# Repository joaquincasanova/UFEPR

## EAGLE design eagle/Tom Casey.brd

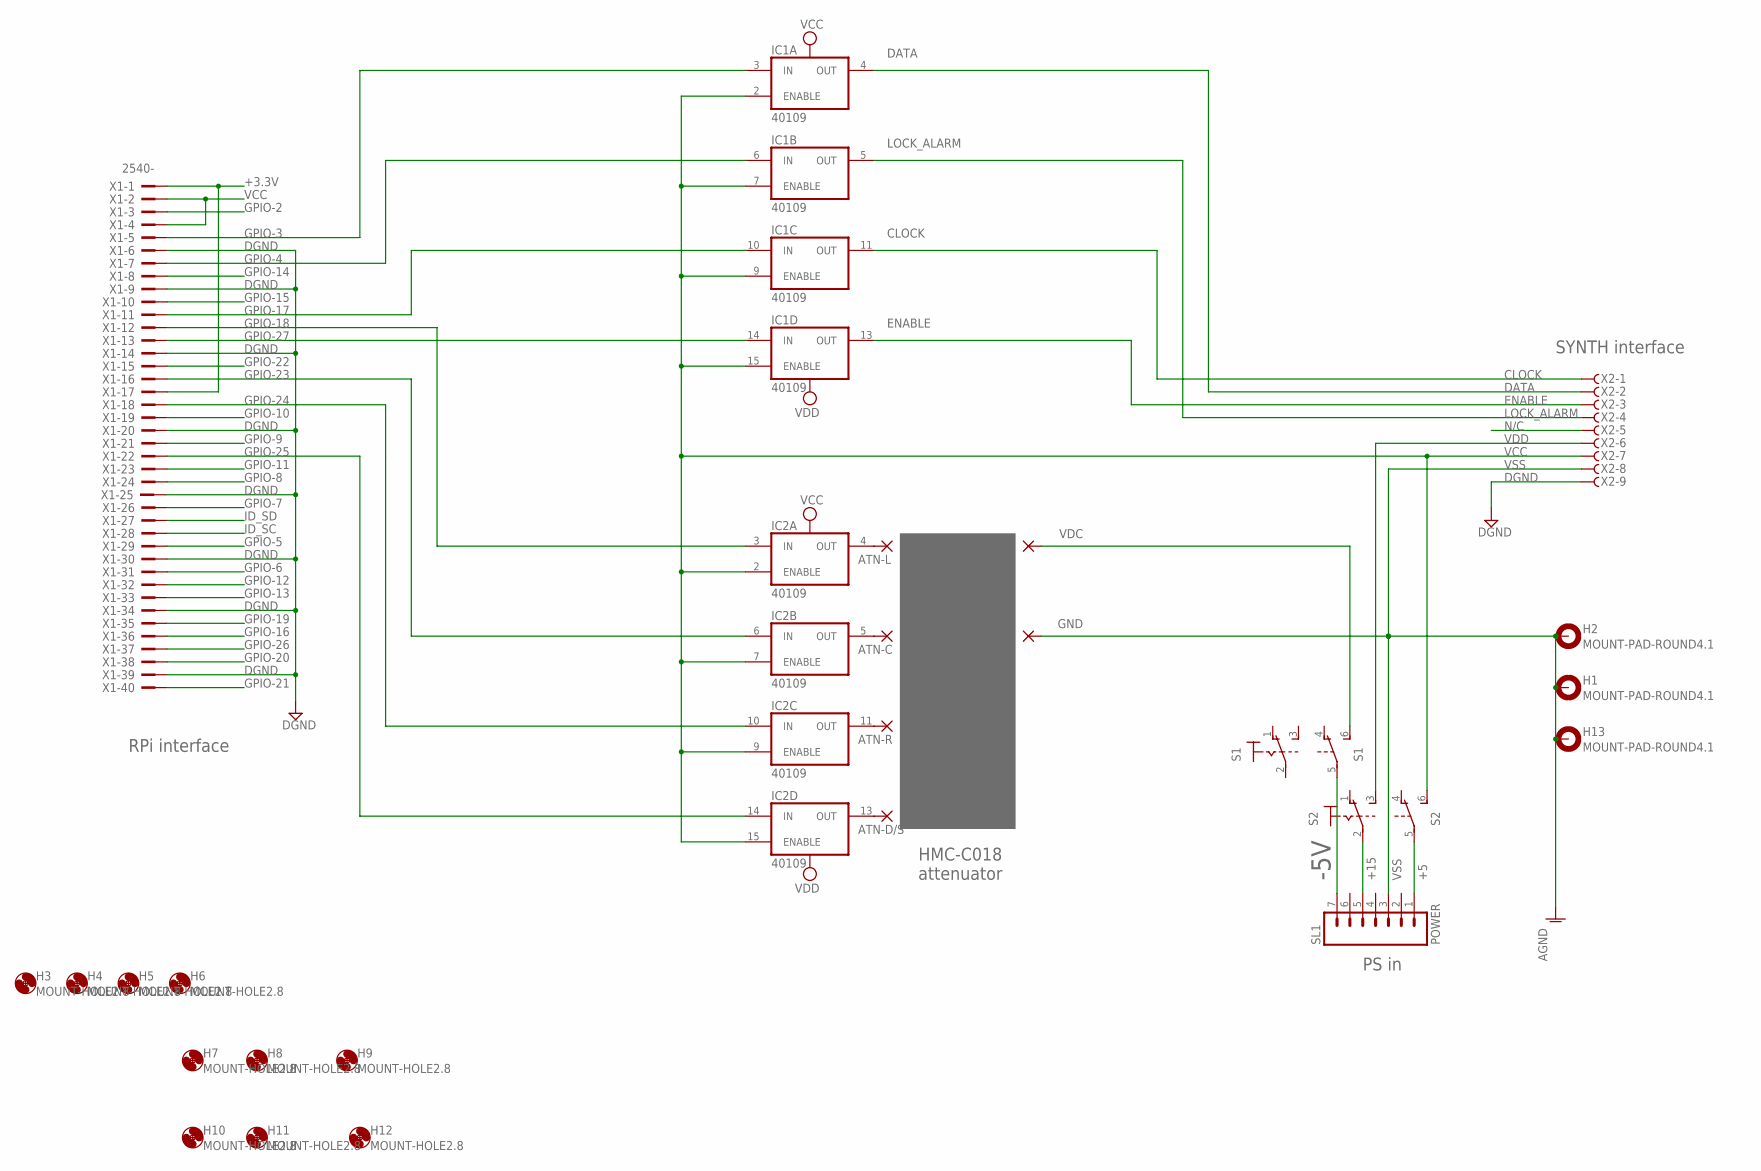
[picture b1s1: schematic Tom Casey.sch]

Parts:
ATN-C: PAD-0400; 0400
ATN-D/S: PAD-0400; 0400
ATN-L: PAD-0400; 0400
ATN-R: PAD-0400; 0400
GND: PAD-0400; 0400
H1, H2, H13: MOUNT-PAD-ROUND4.1; 4,1-PAD
H3, H4, H5, H6, H7, H8, H9, H10, H11, H12: MOUNT-HOLE2.8; 2,8
IC1, IC2: 40109; DIL16
S1, S2: M9040P2
SL1: POWER; 07P
VDC: PAD-0400; 0400
X1: 2540-; PAK100/2500-40
X2: F09HPS; F09HP

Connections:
+3.3V: X1.1, X1.17
+5: S2.5, SL1.1
+15: S2.2, SL1.5
-5V: S1.5, SL1.7
CLOCK: IC1.11 (OUT), X2.1
DATA: IC1.4 (OUT), X2.2
DGND: X1.6, X1.9, X1.14, X1.20, X1.25, X1.30, X1.34, X1.39, X2.9
ENABLE: IC1.13 (OUT), X2.3
GPIO-2: X1.3
GPIO-3: IC1.3 (IN), X1.5
GPIO-4: IC1.6 (IN), X1.7
GPIO-5: X1.29
GPIO-6: X1.31
GPIO-7: X1.26
GPIO-8: X1.24
GPIO-9: X1.21
GPIO-10: X1.19
GPIO-11: X1.23
GPIO-12: X1.32
GPIO-13: X1.33
GPIO-14: X1.8
GPIO-15: X1.10
GPIO-16: X1.36
GPIO-17: IC1.10 (IN), X1.11
GPIO-18: IC2.3 (IN), X1.12
GPIO-19: X1.35
GPIO-20: X1.38
GPIO-21: X1.40
GPIO-22: X1.15
GPIO-23: IC2.6 (IN), X1.16
GPIO-24: IC2.10 (IN), X1.18
GPIO-25: IC2.14 (IN), X1.22
GPIO-26: X1.37
GPIO-27: IC1.14 (IN), X1.13
ID_SC: X1.28
ID_SD: X1.27
LOCK_ALARM: IC1.5 (OUT), X2.4
unnamed: ATN-L.P$1, IC2.4 (OUT)
unnamed: ATN-C.P$1, IC2.5 (OUT)
unnamed: ATN-R.P$1, IC2.11 (OUT)
unnamed: ATN-D/S.P$1, IC2.13 (OUT)
unnamed: S1.6 (S), VDC.P$1
N/C: X2.5
VCC: IC1.1 (VCC), IC1.2 (ENABLE), IC1.7 (ENABLE), IC1.9 (ENABLE), IC1.15 (ENABLE), IC2.1 (VCC), IC2.2 (ENABLE), IC2.7 (ENABLE), IC2.9 (ENABLE), IC2.15 (ENABLE), S2.6 (S), X1.2, X1.4, X2.7
VDD: IC1.16 (VDD), IC2.16 (VDD), S2.3 (S), X2.6
VSS: GND.P$1, H1.B4,1, H2.B4,1, H13.B4,1, IC1.8 (VSS), IC2.8 (VSS), SL1.3, X2.8, X2.G1

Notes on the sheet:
PS in
HMC-C018 attenuator
RPi interface
SYNTH interface

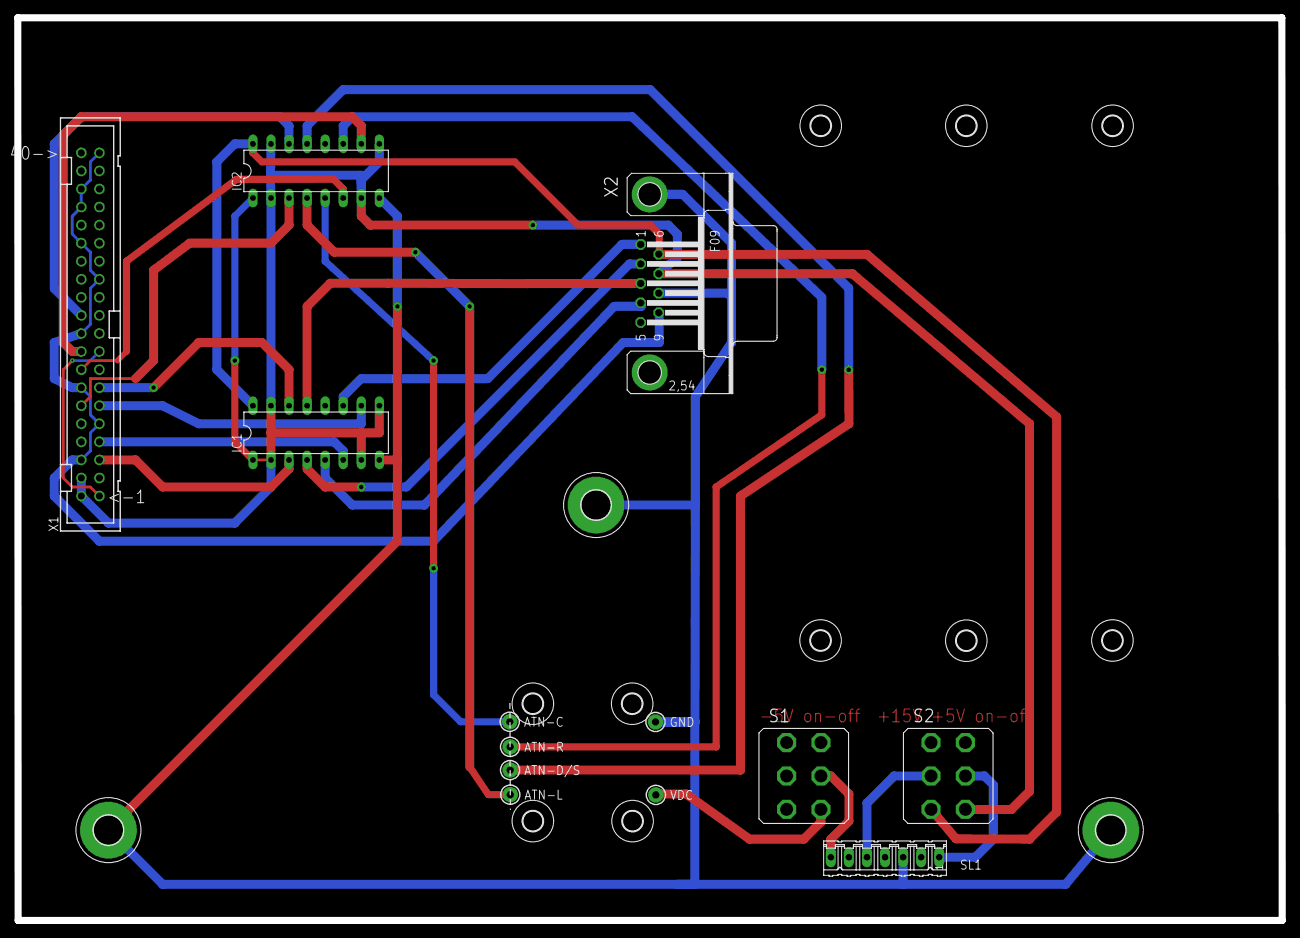
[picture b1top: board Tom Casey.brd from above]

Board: 2 copper layers, 177.8 x 126.9 mm, 26 parts (0 on the bottom side), 25 nets.

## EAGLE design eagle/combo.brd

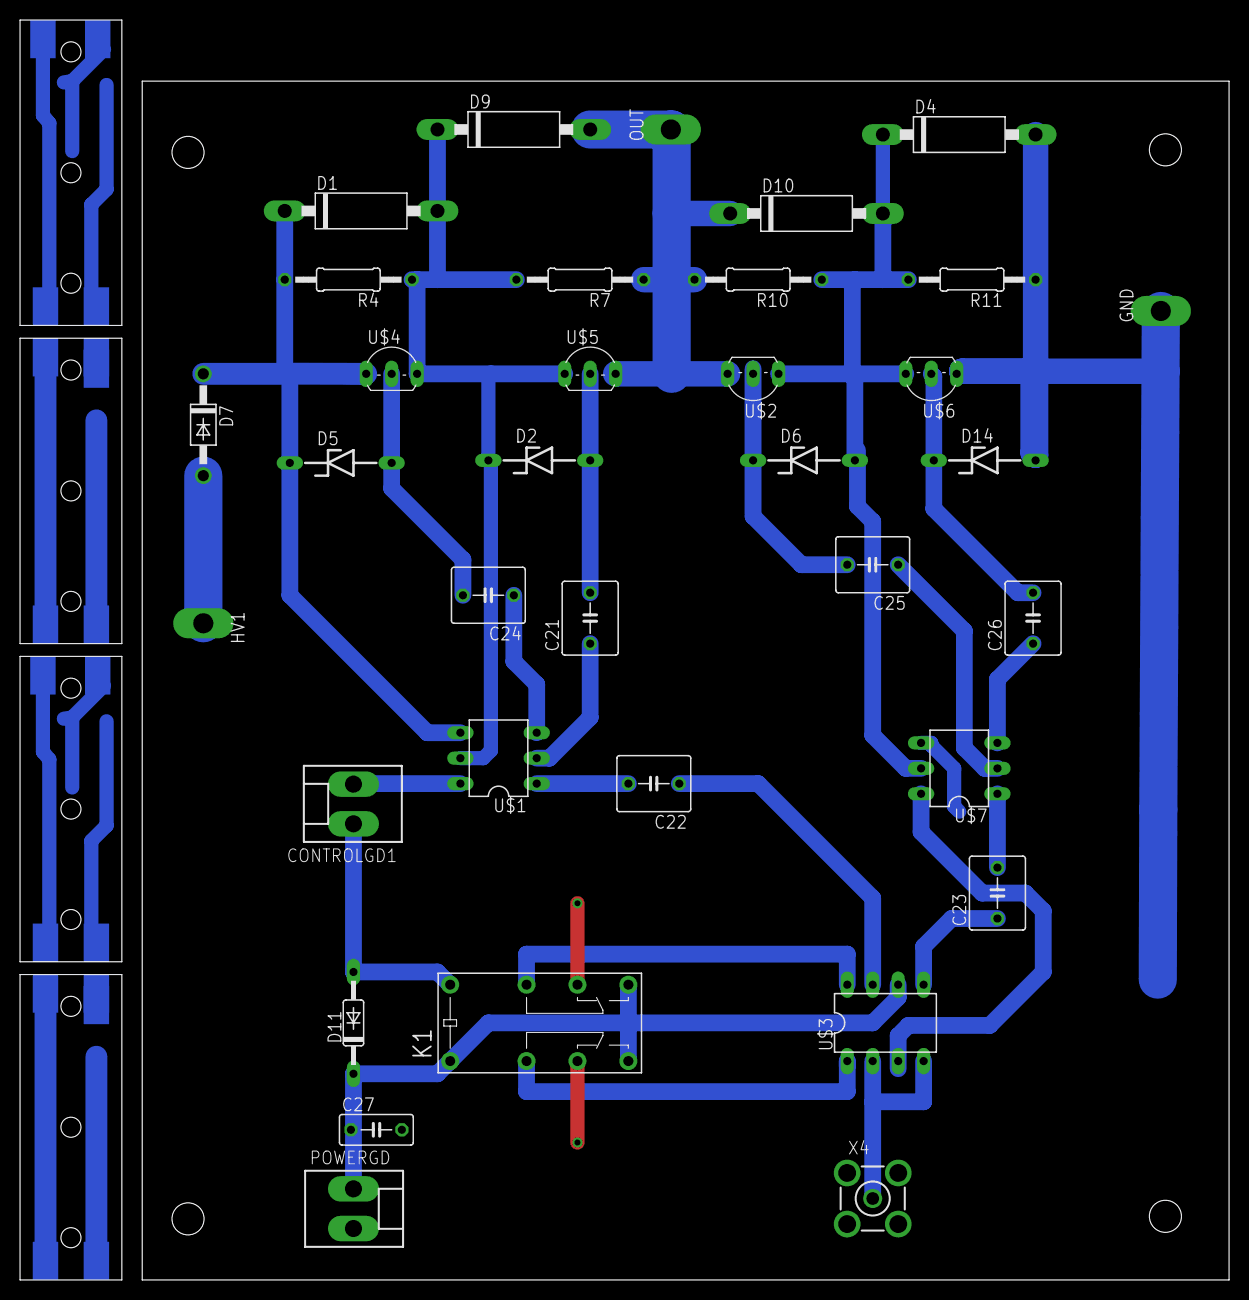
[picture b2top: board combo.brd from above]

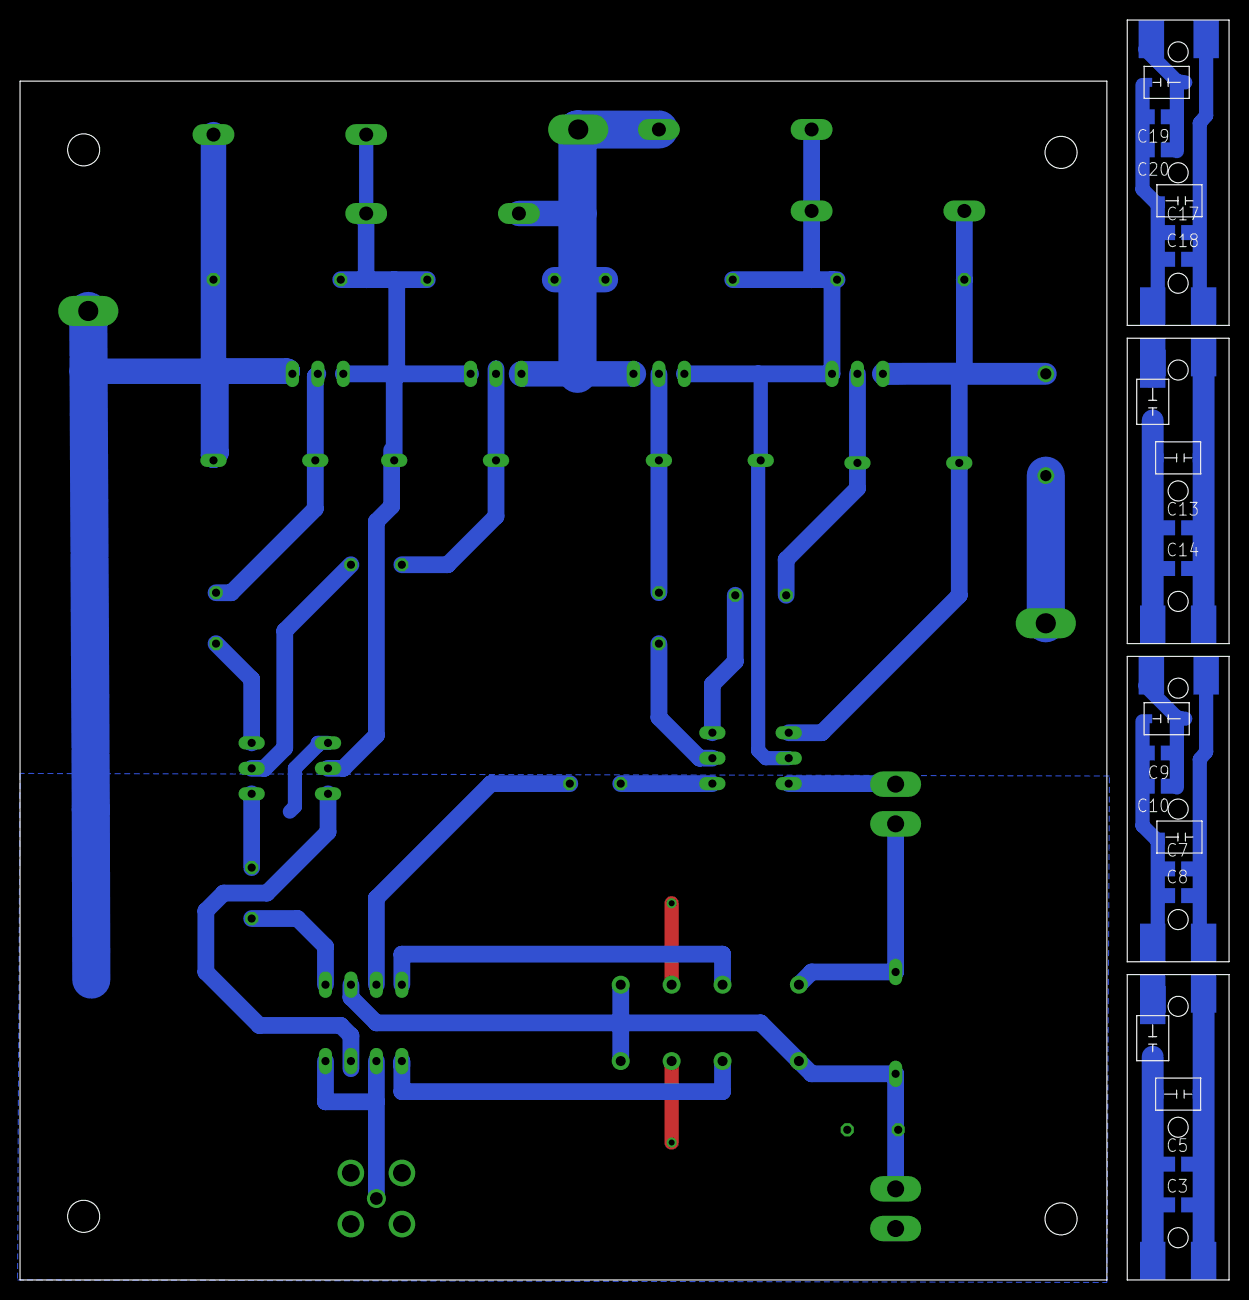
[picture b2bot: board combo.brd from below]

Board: 2 copper layers, 120.7 x 125.7 mm, 55 parts (20 on the bottom side), 33 nets.

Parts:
C1, C4, C6, C11, C15, C16: 5-20; SGC3S
C2, C12: 10-30; SGC3S
C3, C14: 100p; C0805
C5, C13: 50p; C0805
C7, C17: 1000; C0805
C8, C18: 220; C0805
C9, C19: 220p; C0805
C10, C20: 1000p; C0805
C21, C22, C23, C24, C25, C26: C050-055X075
C27: C050-030X075
CONTROLGD1: KK-156-2
D1, D4, D9, D10: P6KEXXA; C1702-15
D2, D5, D6, D14: 4742; ZDIO-10
D7: 1N4004; DO41-10
D11: 1N4148DO35-10; DO35-10
GND: TPPAD1-20Y; P1-20Y
HV1: TPPAD1-20Y; P1-20Y
K1: G5V-2
OUT: TPPAD1-20Y; P1-20Y
POWERGD: KK-156-2
R4, R7, R10, R11: 10M; 0207/12
U$1, U$7: DA-2320; DIL06
U$2, U$6: VN0550; TO92-
U$3: UCC27425; DIL08
U$4, U$5: VP0550; TO92-
X4: BU-SMA-V

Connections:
+15V: C27.1, D11.C, K1.1, K1.8, K1.9, POWERGD.1, U$3.6
ENSW: CONTROLGD1.1, D11.A, K1.16
GND: C27.2, CONTROLGD1.2, D4.A, D14.A, GND.TP, K1.6, K1.11, POWERGD.2, R11.1, U$1.6, U$3.3, U$6.3, U$7.4, U$7.6, X4.2, X4.3, X4.4, X4.5
unnamed: C1.P$1, C2.P$2, C3.1, C5.1
unnamed: C4.P$1, C6.P$2, C7.1, C8.1, C9.2, C10.2
unnamed: C4.P$2, C9.1, C10.1
unnamed: C7.2, C8.2
unnamed: C11.P$1, C12.P$2, C13.1, C14.1
unnamed: C3.2, C5.2
unnamed: C13.2, C14.2
unnamed: C15.P$1, C16.P$2, C17.1, C18.1, C19.2, C20.2
unnamed: C15.P$2, C19.1, C20.1
unnamed: C17.2, C18.2
unnamed: U$3.2, U$3.4, X4.1
unnamed: C22.2, U$1.1
unnamed: C22.1, U$3.7
unnamed: C23.1, U$3.5
unnamed: K1.4, U$3.1
unnamed: K1.13, U$3.8
unnamed: C21.1, U$1.2
unnamed: C24.1, U$1.3
unnamed: C21.2, D2.A, U$5.2
unnamed: C25.1, U$7.2
unnamed: C26.1, U$7.3
unnamed: C24.2, D5.A, U$4.2
unnamed: C25.2, D6.C, U$2.2
unnamed: D1.C, D5.C, D7.C, R4.2, U$1.4, U$4.3
unnamed: C26.2, D14.C, U$6.2
unnamed: D9.A, D10.C, OUT.TP, R7.1, R10.2, U$2.1, U$5.1
unnamed: D7.A, HV1.TP
unnamed: C23.2, U$7.1
unnamed: D4.C, D6.A, D10.A, R10.1, R11.2, U$2.3, U$6.1
unnamed: D1.A, D2.C, D9.C, R4.1, R7.2, U$1.5, U$4.1, U$5.3

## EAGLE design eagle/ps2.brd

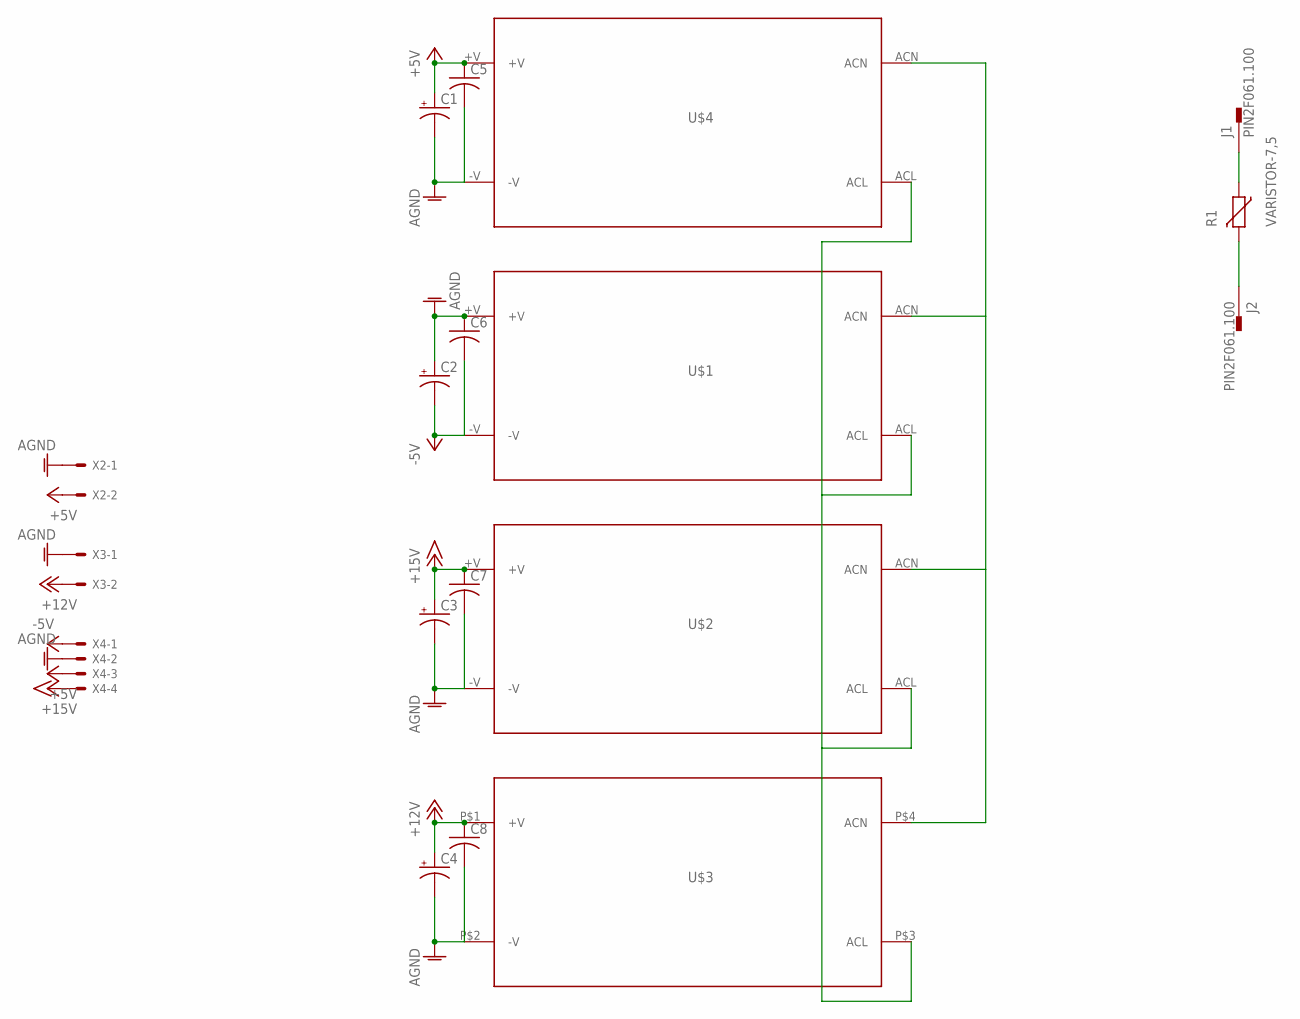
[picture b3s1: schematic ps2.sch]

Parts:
C1, C2, C3, C4: CPOL-USE10-22.5; EB22,5D
C5, C6, C7, C8: C-US075-052X106; C075-052X106
J1, J2: PIN2F061.100; F061.100
R1: VARISTOR-7,5; R-7,5
U$1, U$4: IRM-30-5; IRM-30-15
U$2: IRM-30-15
U$3: IRM-60-12
X2, X3: KK-156-2
X4: KK-156-4

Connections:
+5V: C1.+, C5.1, U$4.+V, X2.2, X4.3
+12V: C4.+, C8.1, U$3.P$1 (+V), X3.2
+15V: C3.+, C7.1, U$2.+V, X4.4
-5V: C2.-, C6.2, U$1.-V, X4.1
ACL: J1.A1, J1.A2, R1.1, U$1.ACL, U$2.ACL, U$3.P$3 (ACL), U$4.ACL
ACN: J2.A1, J2.A2, R1.2, U$1.ACN, U$2.ACN, U$3.P$4 (ACN), U$4.ACN
AGND: C1.-, C2.+, C3.-, C4.-, C5.2, C6.1, C7.2, C8.2, U$1.+V, U$2.-V, U$3.P$2 (-V), U$4.-V, X2.1, X3.1, X4.2

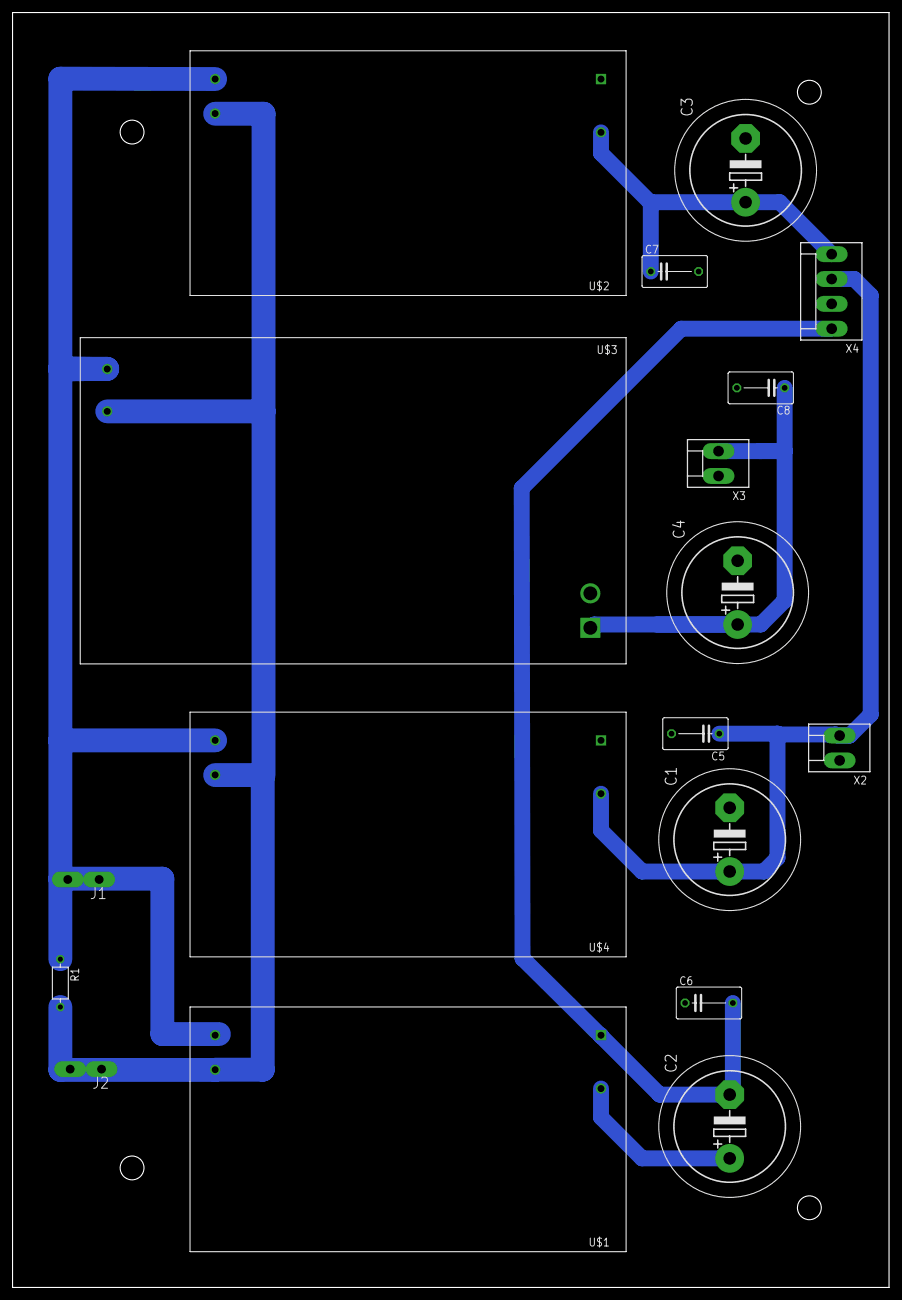
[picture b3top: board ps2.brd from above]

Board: 2 copper layers, 139.7 x 203.2 mm, 18 parts (0 on the bottom side), 7 nets.

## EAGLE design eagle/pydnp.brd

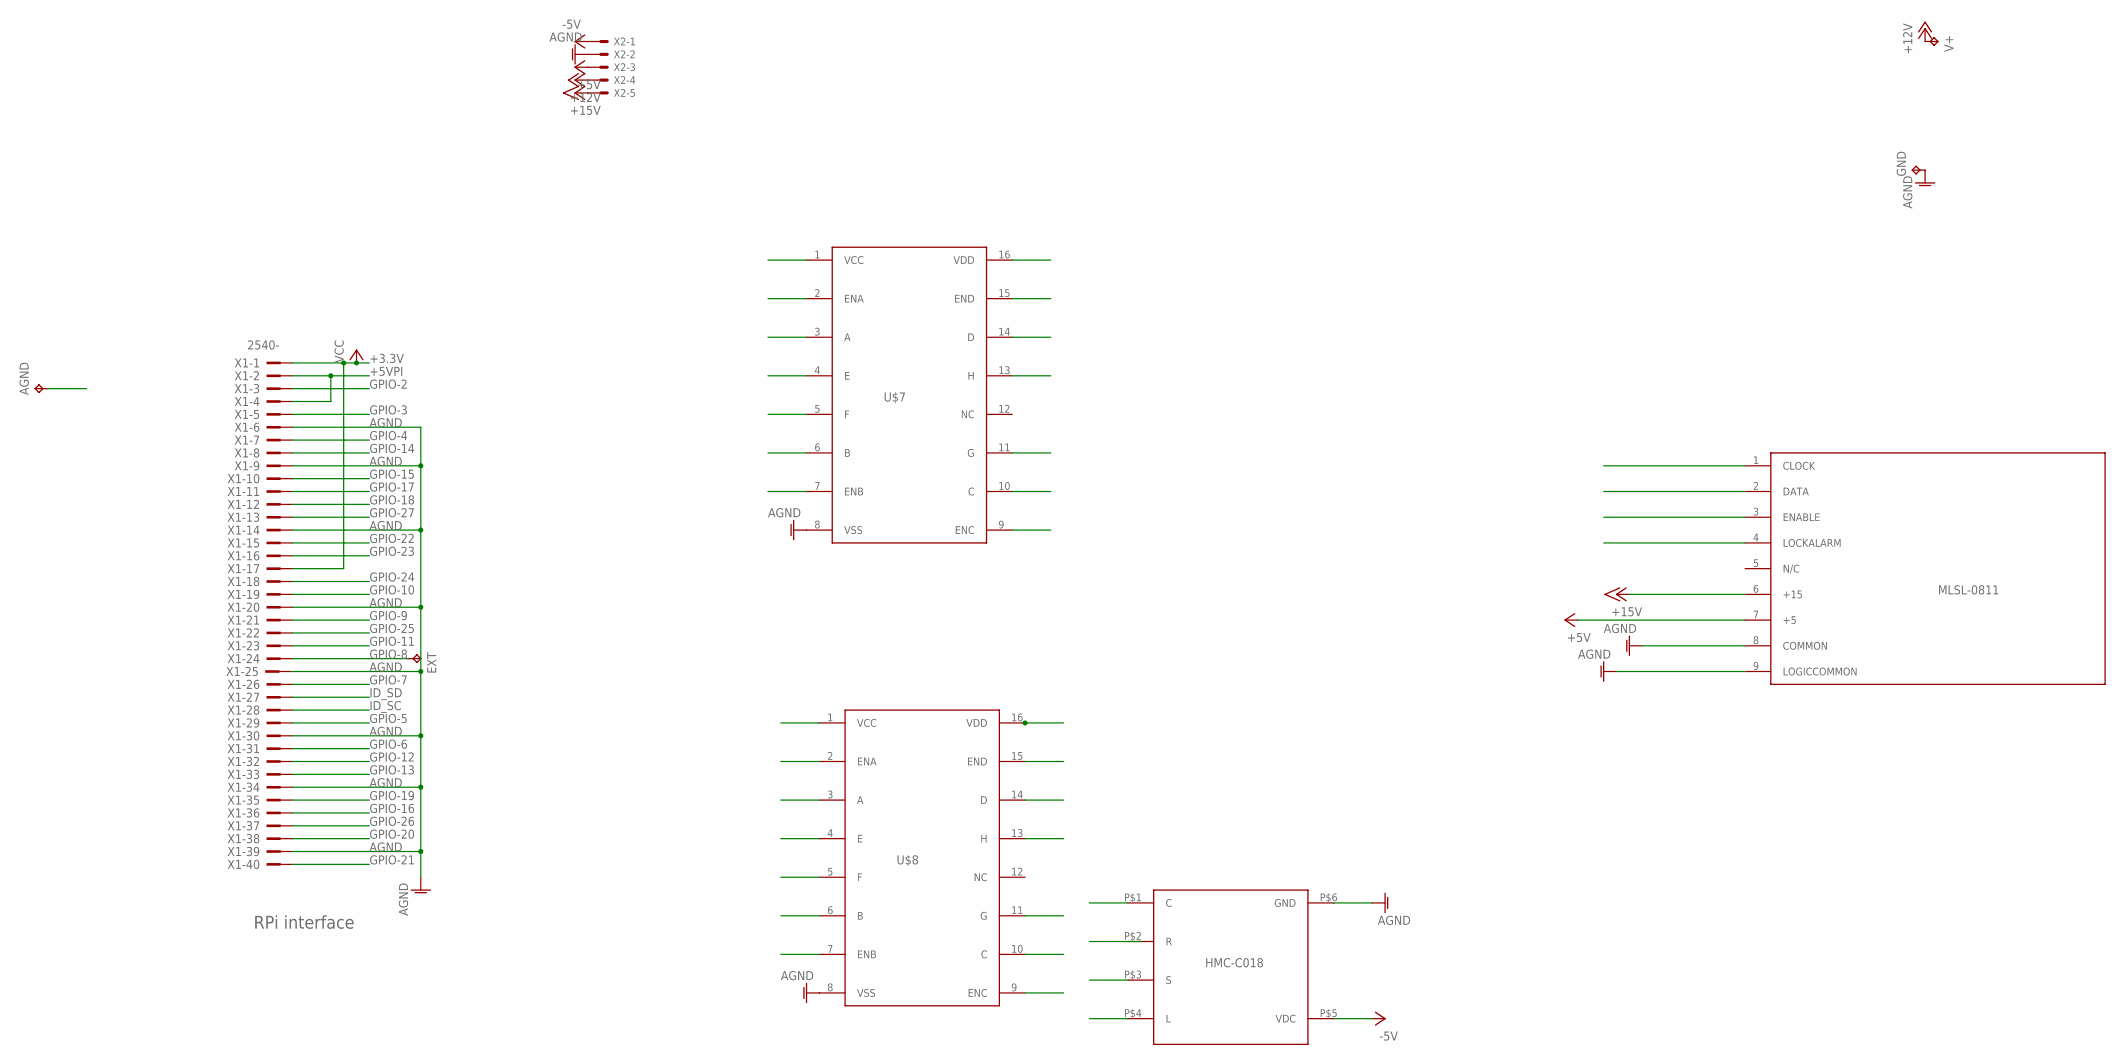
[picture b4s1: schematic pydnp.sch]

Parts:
AGND: TPPAD1-20Y; P1-20Y
EXT: TPPAD1-20Y; P1-20Y
GND: TPPAD1-20Y; P1-20Y
U$1: MLSLCORRECT; 177-009-FEMALE
U$2: HMC-C018
U$7, U$8: 40109; DIL16
V+: TPPAD1-20Y; P1-20Y
X1: 2540-; PAK100/2500-40
X2: KK-156-5

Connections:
+3.3V: U$7.1 (VCC), U$7.2 (ENA), U$7.7 (ENB), U$7.9 (ENC), U$7.15 (END), U$8.1 (VCC), U$8.2 (ENA), U$8.7 (ENB), U$8.9 (ENC), U$8.15 (END), X1.1, X1.17
+5V: U$1.7 (+5), X2.3
+5VPI: U$7.16 (VDD), U$8.16 (VDD), X1.2, X1.4
+12V: V+.TP, X2.4
+15V: U$1.6 (+15), X2.5
-5V: U$2.P$5 (VDC), X2.1
AGND: AGND.TP, GND.TP, U$1.8 (COMMON), U$1.9 (LOGICCOMMON), U$2.P$6 (GND), U$7.8 (VSS), U$8.8 (VSS), X1.6, X1.9, X1.14, X1.20, X1.25, X1.30, X1.34, X1.39, X2.2
C: U$2.P$1 (C), U$8.4 (E)
CLOCK: U$1.1 (CLOCK), U$7.4 (E)
DATA: U$1.2 (DATA), U$7.13 (H)
ENABLE: U$1.3 (ENABLE), U$7.11 (G)
GPIO-2: X1.3
GPIO-3: X1.5
GPIO-4: U$7.10 (C), X1.7
GPIO-5: X1.29
GPIO-6: X1.31
GPIO-7: X1.26
GPIO-8: EXT.TP, X1.24
GPIO-9: X1.21
GPIO-10: X1.19
GPIO-11: X1.23
GPIO-12: X1.32
GPIO-13: X1.33
GPIO-14: X1.8
GPIO-15: X1.10
GPIO-16: X1.36
GPIO-17: U$7.6 (B), X1.11
GPIO-18: U$8.14 (D), X1.12
GPIO-19: X1.35
GPIO-20: X1.38
GPIO-21: X1.40
GPIO-22: U$7.14 (D), X1.15
GPIO-23: U$8.3 (A), X1.16
GPIO-24: U$8.6 (B), X1.18
GPIO-25: U$8.10 (C), X1.22
GPIO-26: X1.37
GPIO-27: U$7.3 (A), X1.13
ID_SC: X1.28
ID_SD: X1.27
L: U$2.P$4 (L), U$8.5 (F)
LOCK_ALARM: U$1.4 (LOCKALARM), U$7.5 (F)
R: U$2.P$2 (R), U$8.13 (H)
S: U$2.P$3 (S), U$8.11 (G)

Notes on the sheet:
RPi interface
GPIO-27

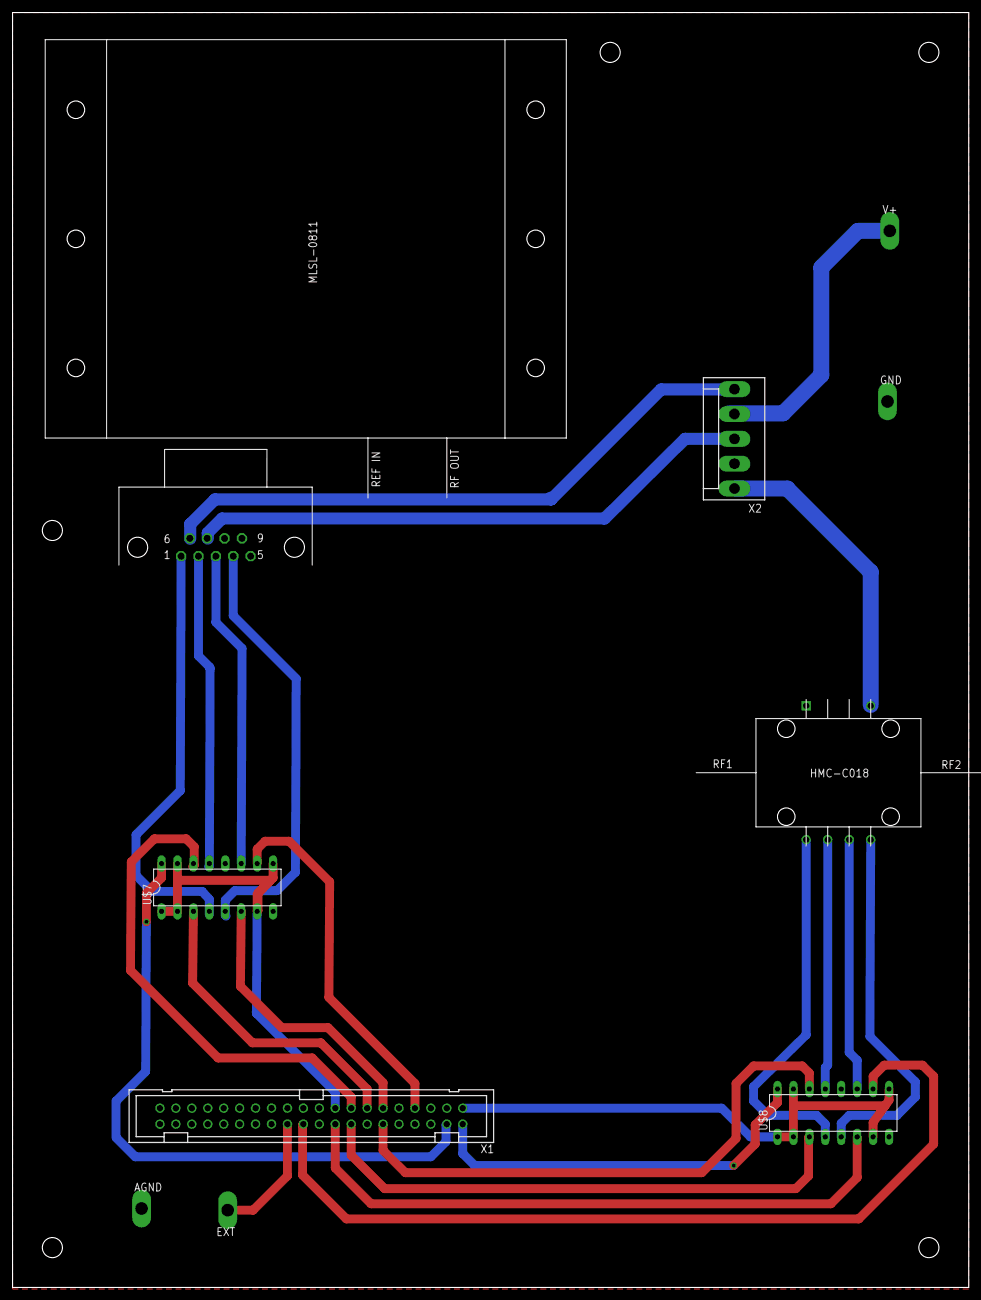
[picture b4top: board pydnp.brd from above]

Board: 2 copper layers, 152.4 x 203.2 mm, 10 parts (0 on the bottom side), 24 nets.

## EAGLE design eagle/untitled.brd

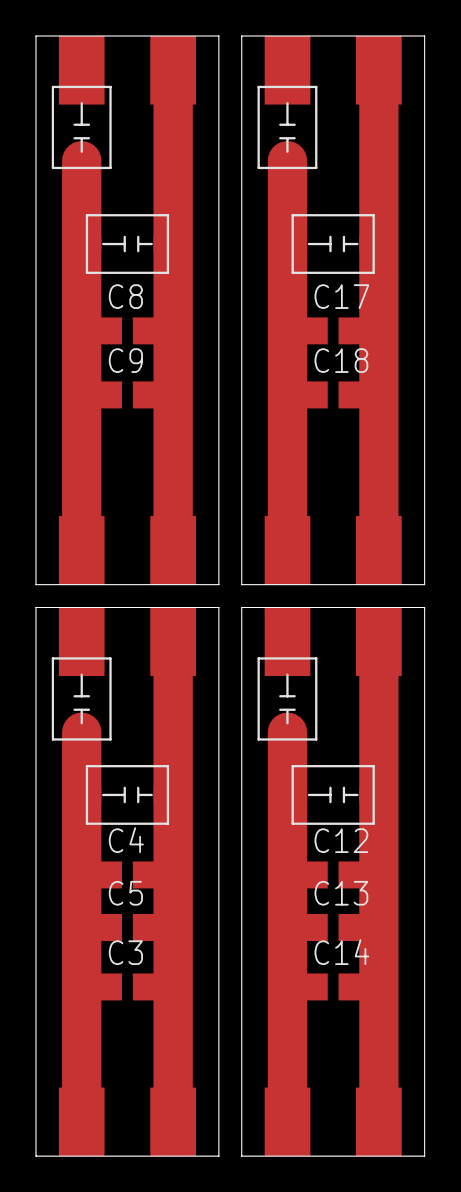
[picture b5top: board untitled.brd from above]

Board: 2 copper layers, 21.6 x 62.2 mm, 18 parts (0 on the bottom side), 8 nets.

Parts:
C1, C6, C10, C15: 5-20; SGC3S
C2, C7, C11, C16: 10-30; SGC3S
C3, C4, C8, C12, C14, C17: 100p; C0805
C5, C9, C13, C18: 50p; C0805

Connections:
unnamed: C1.P$1, C2.P$2, C3.1, C4.1, C5.1
unnamed: C6.P$1, C7.P$2, C8.1, C9.1
unnamed: C8.2, C9.2
unnamed: C10.P$1, C11.P$2, C12.1, C13.1, C14.1
unnamed: C3.2, C4.2, C5.2
unnamed: C12.2, C13.2, C14.2
unnamed: C15.P$1, C16.P$2, C17.1, C18.1
unnamed: C17.2, C18.2

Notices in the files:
parts and their libraries:
dpads: Copyright (C) 2004, Bob Starr (bobstarr@mindspring.com)
